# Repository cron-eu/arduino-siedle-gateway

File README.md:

Arduino Doorbell
====

Abstract
----

This repository holds the documentation and software needed to build a Slack interface to our Siedle Doorbell-System, using an Arduino MKR 1010 WiFi board and some electronics.

The gateway is being migrated to ESP32 / ESP-IDF (`firmware-idf/`), which will also add audio support. Until the new firmware runs in production, the Arduino firmware stays in `firmware/`.

Project Folder Structure
---

* `firmware-idf/**` New firmware for ESP32 / ESP32-S3 boards (ESP-IDF, C), see [firmware-idf/README.md](firmware-idf/README.md)
* `firmware/**` Firmware for the Arduino MKR1010 WiFi Board (C++)
* `lambda/**` AWS Lambda functions (Slack integration)
* `hardware/**` Schematics (Eagle)
* `doc/**` Documentation, see [doc/README.md](doc/README.md)

Author
----

Remus Lazar (rl -at- cron dot eu)

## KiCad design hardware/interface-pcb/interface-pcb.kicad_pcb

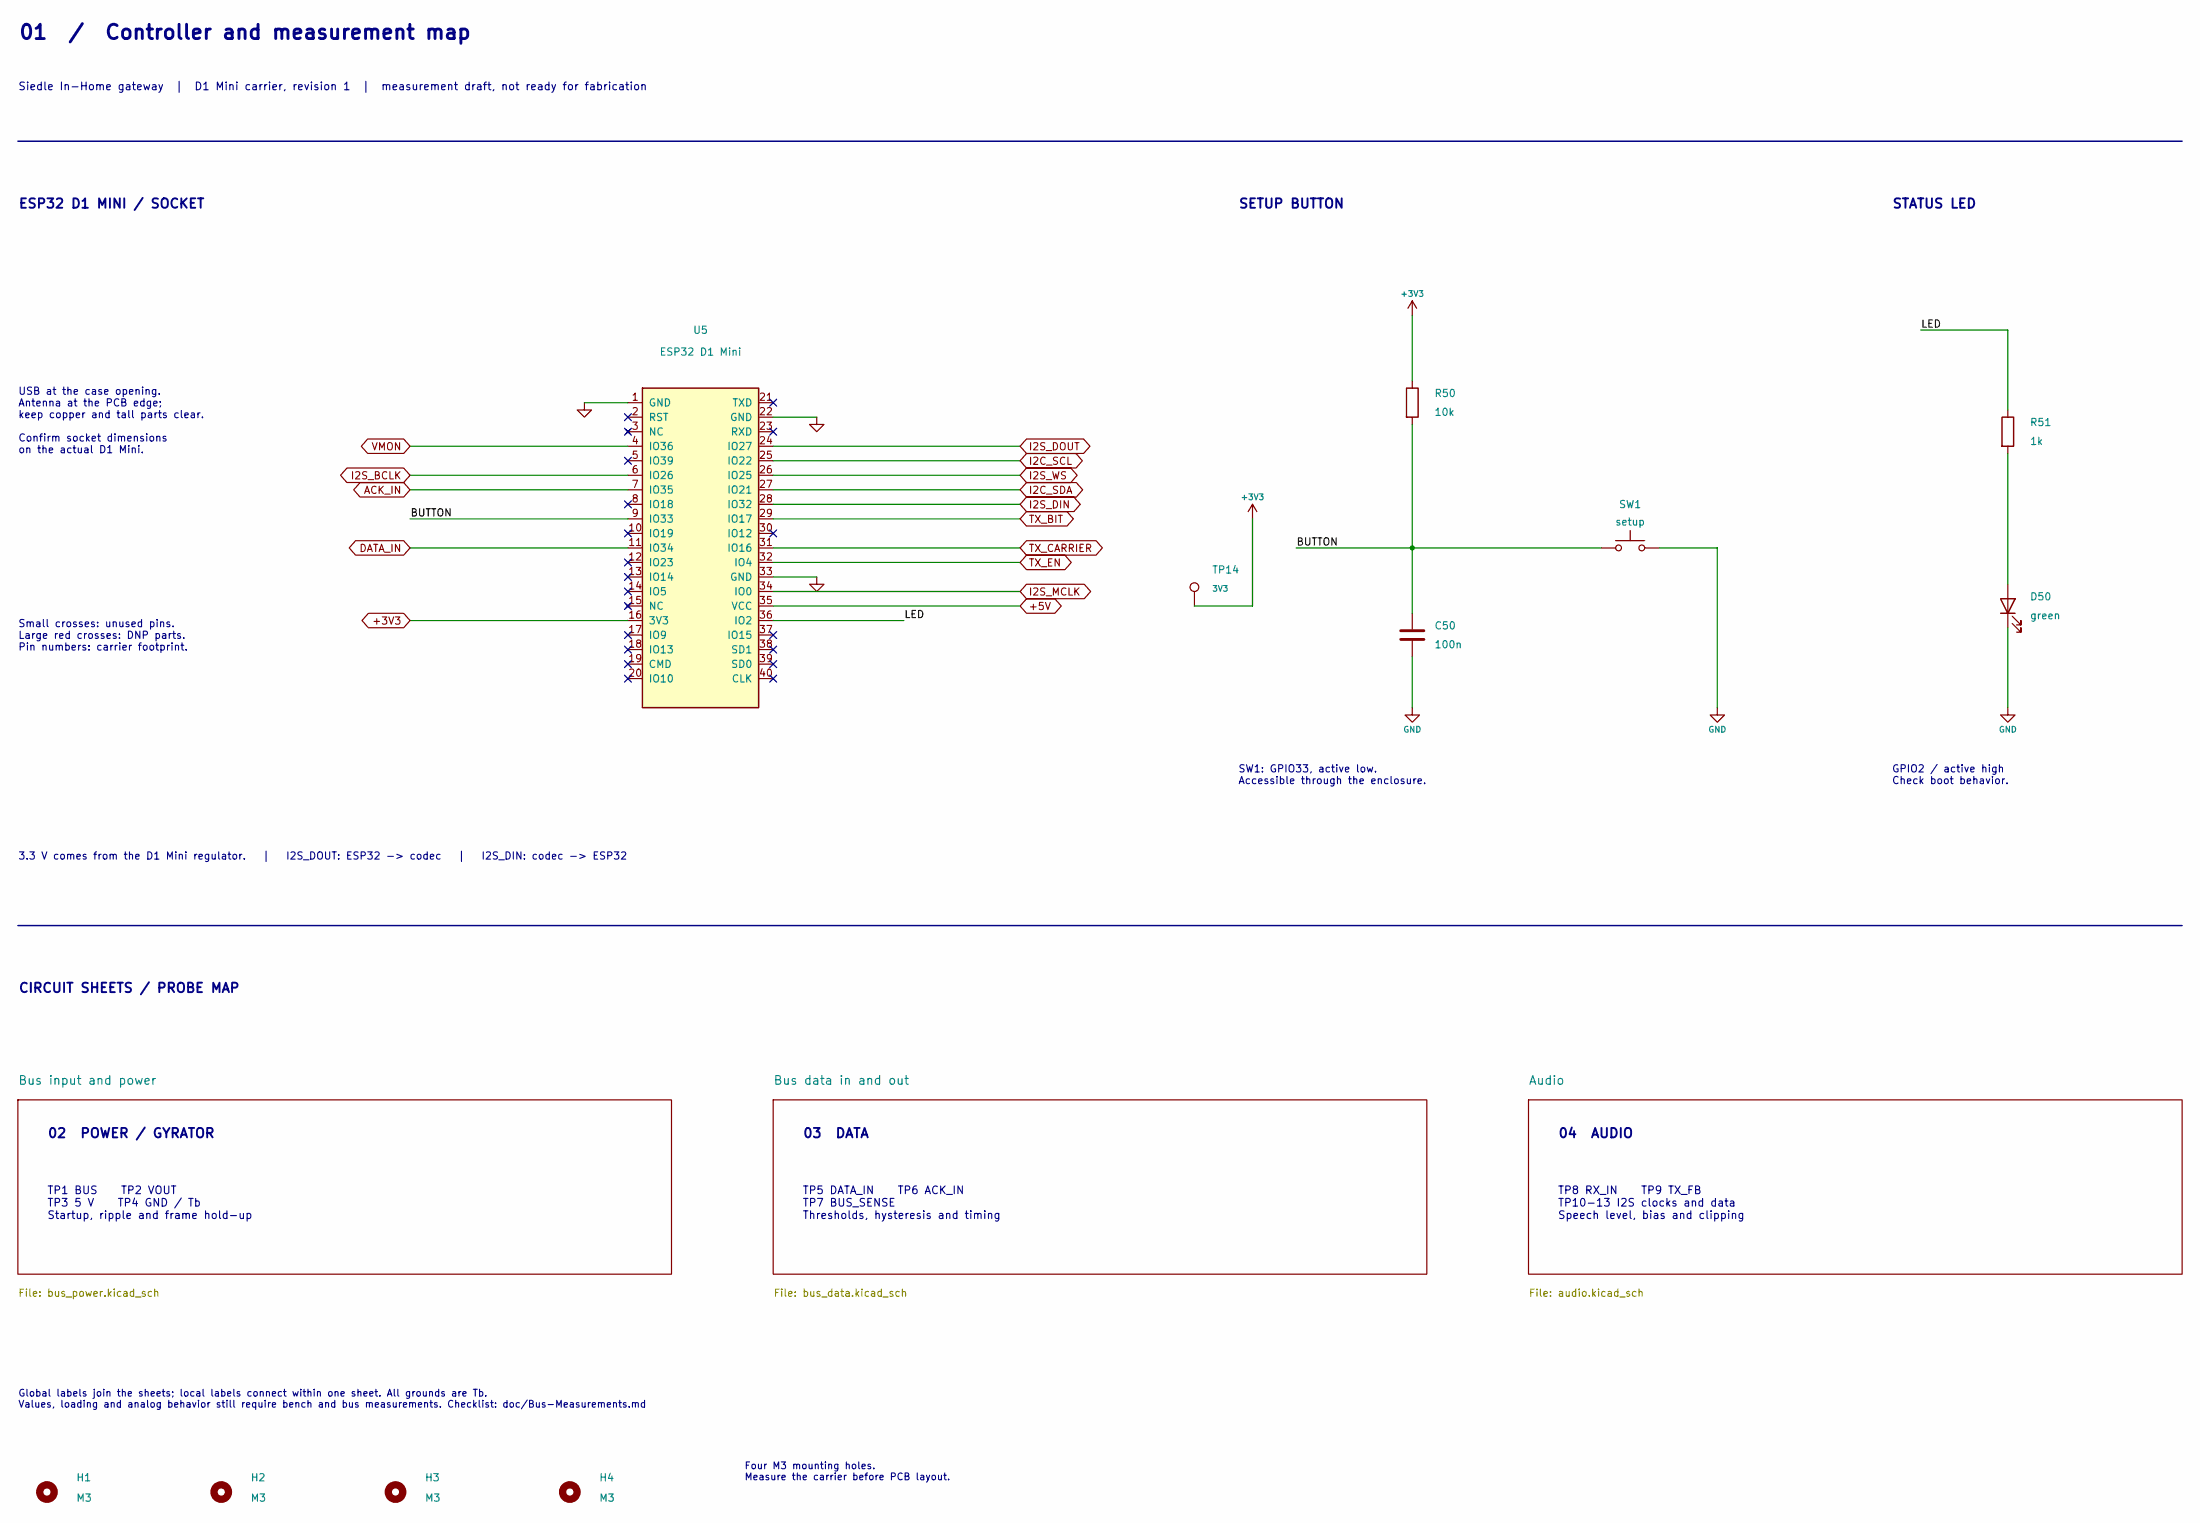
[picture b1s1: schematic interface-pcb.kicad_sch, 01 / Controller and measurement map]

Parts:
C50: 100n; C_0805_2012Metric; LCSC C49678
D50: green; LED_0805_2012Metric; LCSC C2297
H1, H2, H3, H4: M3; MountingHole_3.2mm_M3
R50: 10k; R_0805_2012Metric; LCSC C17414
R51: 1k; R_0805_2012Metric
SW1: setup; SW_Push_1P1T_XKB_TS-1187A; LCSC C318884
TP14: 3V3; TestPoint_Pad_D1.5mm
U5: ESP32 D1 Mini; D1_Mini_ESP32_Socket

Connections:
+3V3: R50.1, TP14.1, U5.16 (3V3); also elsewhere on the board
/BUTTON: C50.1, R50.2, SW1.1, U5.9 (IO33)
/LED: R51.1, U5.36 (IO2)
ACK_IN: U5.7 (IO35); also elsewhere on the board
DATA_IN: U5.11 (IO34); also elsewhere on the board
I2C_SCL: U5.25 (IO22); also elsewhere on the board
I2C_SDA: U5.27 (IO21); also elsewhere on the board
I2S_BCLK: U5.6 (IO26); also elsewhere on the board
I2S_DIN: U5.28 (IO32); also elsewhere on the board
I2S_DOUT: U5.24 (IO27); also elsewhere on the board
I2S_MCLK: U5.34 (IO0); also elsewhere on the board
I2S_WS: U5.26 (IO25); also elsewhere on the board
unnamed: D50.2 (A), R51.2
TX_BIT: U5.29 (IO17); also elsewhere on the board
TX_CARRIER: U5.31 (IO16); also elsewhere on the board
TX_EN: U5.32 (IO4); also elsewhere on the board
VMON: U5.4 (IO36); also elsewhere on the board

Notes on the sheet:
01 / Controller and measurement map
Siedle In-Home gateway | D1 Mini carrier, revision 1 | measurement draft, not ready for fabrication
ESP32 D1 MINI / SOCKET
SETUP BUTTON
STATUS LED
USB at the case opening. Antenna at the PCB edge; keep copper and tall parts clear. Confirm socket dimensions on the actual D1 Mini.
Small crosses: unused pins. Large red crosses: DNP parts. Pin numbers: carrier footprint.
SW1: GPIO33, active low. Accessible through the enclosure.
GPIO2 / active high Check boot behavior.
3.3 V comes from the D1 Mini regulator. | I2S_DOUT: ESP32 -> codec | I2S_DIN: codec -> ESP32
CIRCUIT SHEETS / PROBE MAP
02 POWER / GYRATOR
TP1 BUS TP2 VOUT TP3 5 V TP4 GND / Tb Startup, ripple and frame hold-up
03 DATA
TP5 DATA_IN TP6 ACK_IN TP7 BUS_SENSE Thresholds, hysteresis and timing
04 AUDIO
TP8 RX_IN TP9 TX_FB TP10-13 I2S clocks and data Speech level, bias and clipping
Global labels join the sheets; local labels connect within one sheet. All grounds are Tb. Values, loading and analog behavior still require bench and bus measurements. Checklist: doc/Bus-Measurements.md
Four M3 mounting holes. Measure the carrier before PCB layout.

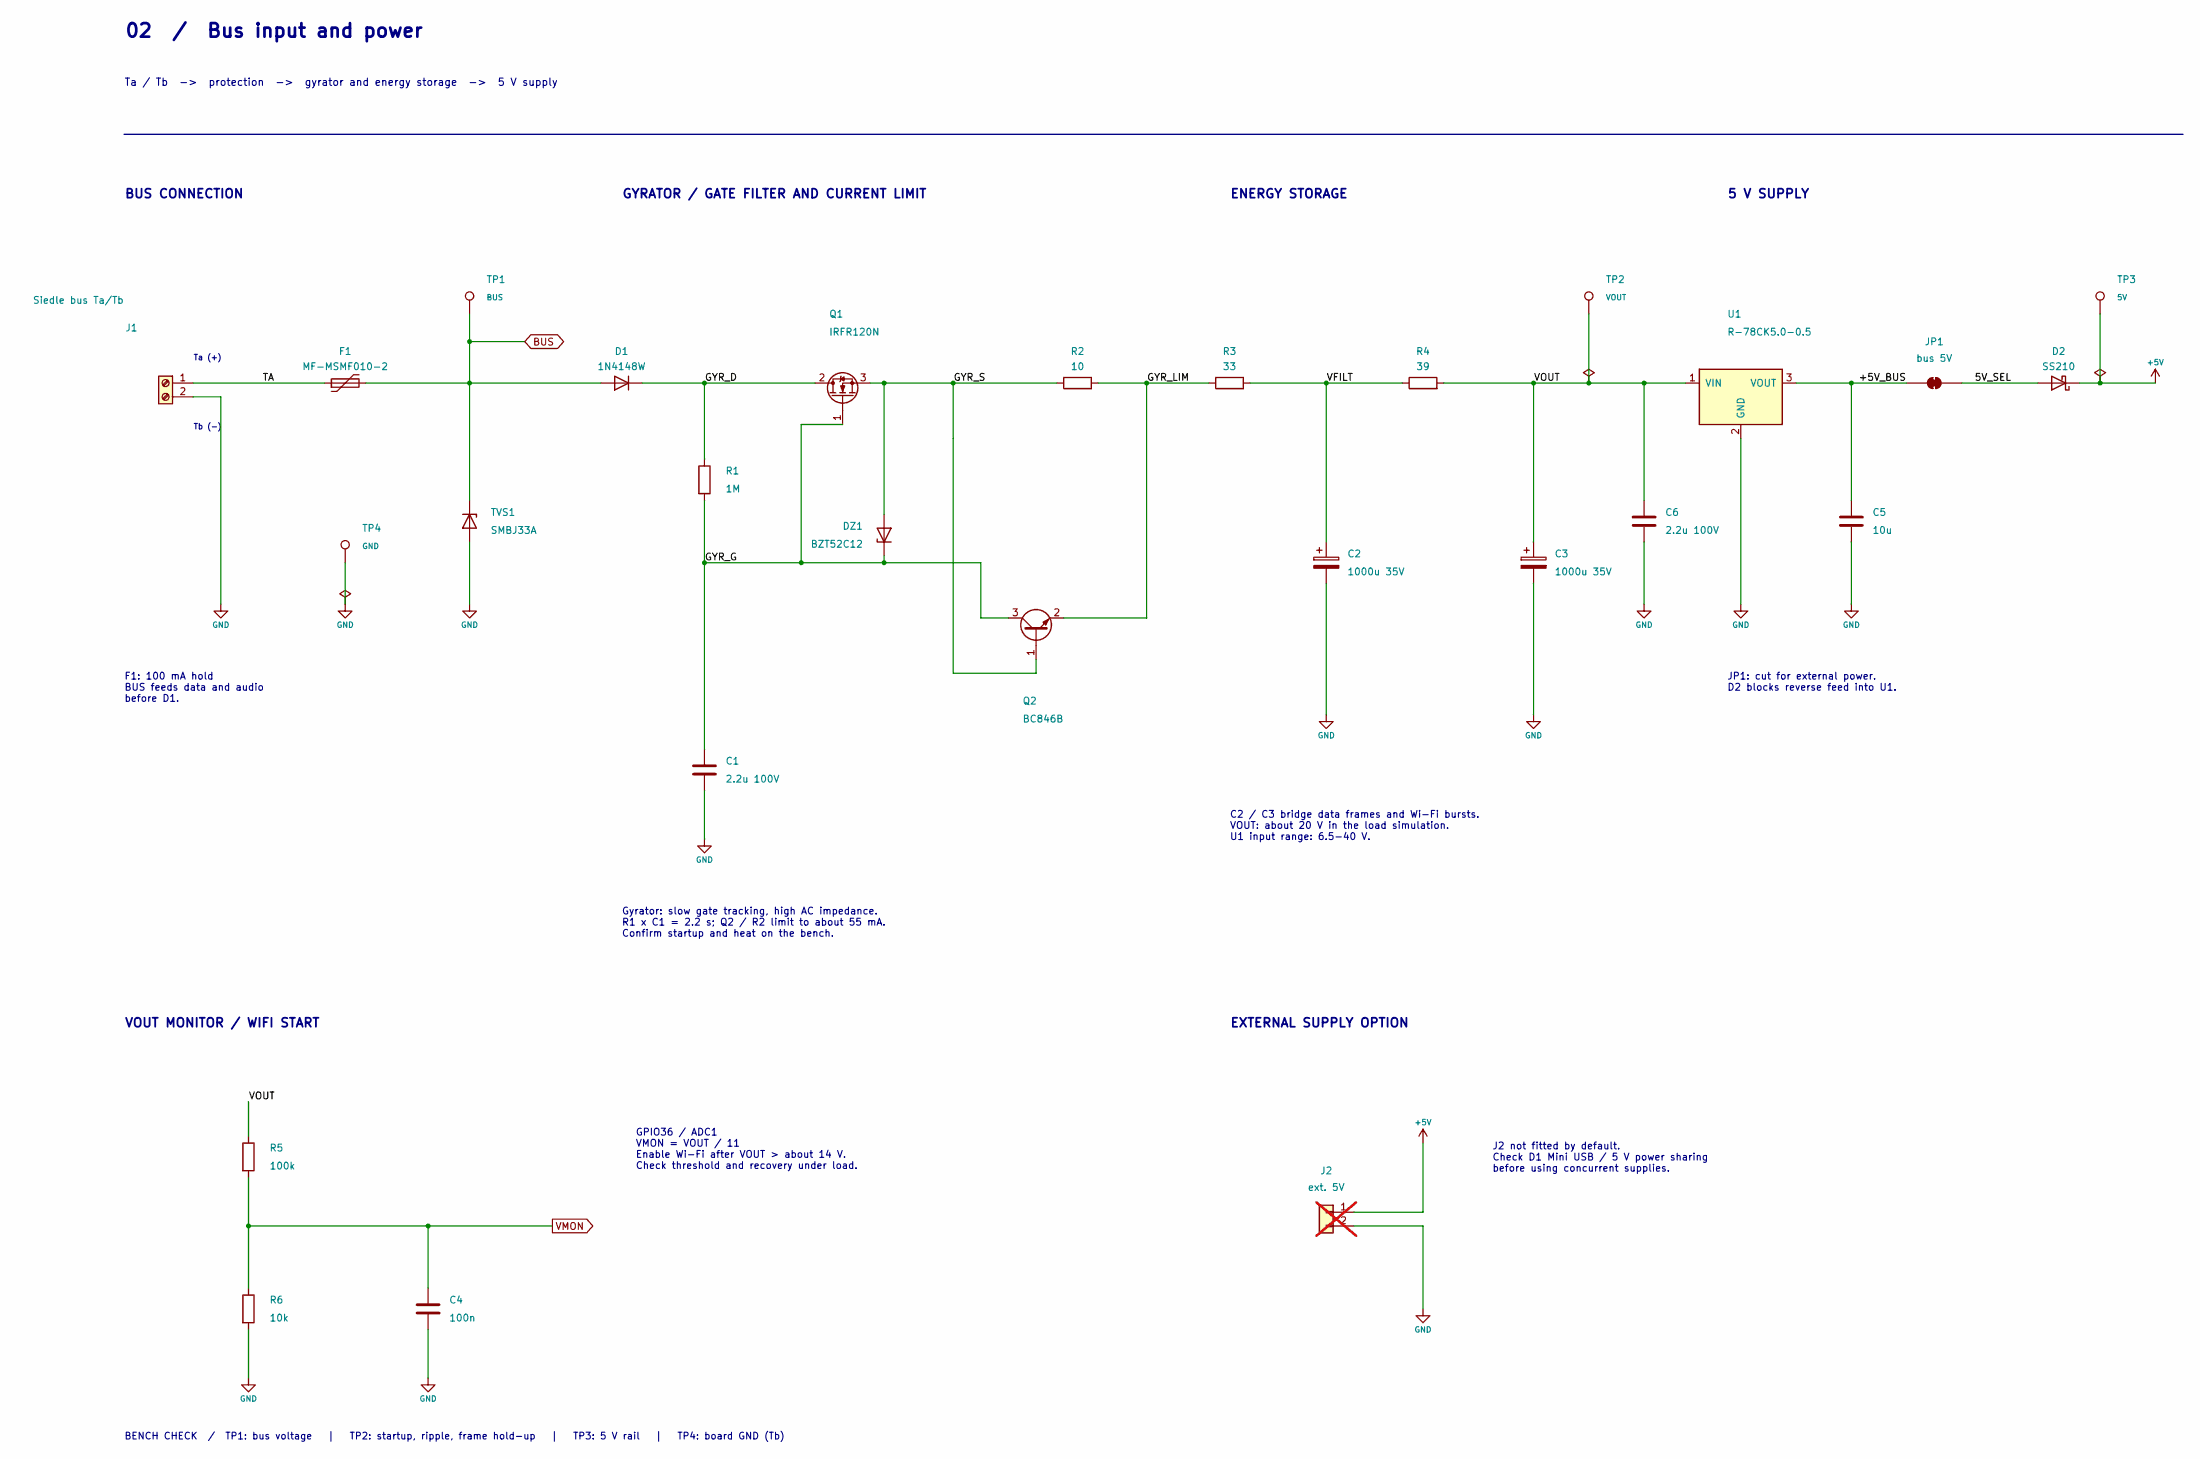
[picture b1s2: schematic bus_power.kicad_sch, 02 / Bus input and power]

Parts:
C1, C6: 2.2u 100V; C_1210_3225Metric; LCSC C153036
C2, C3: 1000u 35V; CP_Radial_D13.0mm_P5.00mm_Lying; LCSC C10749
C4: 100n; C_0805_2012Metric; LCSC C49678
C5: 10u; C_0805_2012Metric; LCSC C15850
D1: 1N4148W; D_SOD-123; LCSC C81598
D2: SS210; D_SMA; LCSC C14996
DZ1: BZT52C12; D_SOD-123; LCSC C19077410
F1: MF-MSMF010-2; Fuse_1812_4532Metric; LCSC C12430
J1: Siedle bus Ta/Tb; TerminalBlock_Phoenix_MKDS-1,5-2-5.08_1x02_P5.08mm_Horizont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; LCSC C474952
J2: ext. 5V; PinHeader_1x02_P2.54mm_Vertical; not fitted
JP1: bus 5V; SolderJumper-2_P1.3mm_Bridged_RoundedPad1.0x1.5mm
Q1: IRFR120N; TO-252-2; LCSC C3008
Q2: BC846B; SOT-23; LCSC C20069134
R1: 1M; R_0805_2012Metric; LCSC C17514
R2: 10; R_0805_2012Metric; LCSC C17415
R3: 33; R_0805_2012Metric; LCSC C17634
R4: 39; R_0805_2012Metric
R5: 100k; R_0805_2012Metric; LCSC C149504
R6: 10k; R_0805_2012Metric; LCSC C17414
TP1: BUS; TestPoint_Pad_D1.5mm
TP2: VOUT; TestPoint_Pad_D1.5mm
TP3: 5V; TestPoint_Pad_D1.5mm
TP4: GND; TestPoint_Pad_D1.5mm
TVS1: SMBJ33A; D_SMB; LCSC C19077586
U1: R-78CK5.0-0.5; Converter_DCDC_RECOM_R-78E-0.5_THT

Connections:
/Bus input and power/5V_SEL: D2.2 (A), JP1.2 (B)
/Bus input and power/+5V_BUS: C5.1, JP1.1 (A), U1.3 (VOUT)
/Bus input and power/GYR_D: D1.1 (K), Q1.2 (D), R1.1
/Bus input and power/GYR_G: C1.1, DZ1.1 (K), Q1.1 (G), Q2.3 (C), R1.2
/Bus input and power/GYR_LIM: Q2.2 (E), R2.2, R3.1
/Bus input and power/GYR_S: DZ1.2 (A), Q1.3 (S), Q2.1 (B), R2.1
/Bus input and power/TA: F1.1, J1.1
/Bus input and power/VFILT: C2.1, R3.2, R4.1
BUS: D1.2 (A), F1.2, TP1.1, TVS1.1 (K); also elsewhere on the board
VMON: C4.1, R5.2, R6.1; also elsewhere on the board

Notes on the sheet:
02 / Bus input and power
Ta / Tb -> protection -> gyrator and energy storage -> 5 V supply
BUS CONNECTION
GYRATOR / GATE FILTER AND CURRENT LIMIT
ENERGY STORAGE
5 V SUPPLY
Ta (+)
Tb (-)
F1: 100 mA hold BUS feeds data and audio before D1.
Gyrator: slow gate tracking, high AC impedance. R1 x C1 = 2.2 s; Q2 / R2 limit to about 55 mA. Confirm startup and heat on the bench.
C2 / C3 bridge data frames and Wi-Fi bursts. VOUT: about 20 V in the load simulation. U1 input range: 6.5-40 V.
JP1: cut for external power. D2 blocks reverse feed into U1.
VOUT MONITOR / WIFI START
GPIO36 / ADC1 VMON = VOUT / 11 Enable Wi-Fi after VOUT > about 14 V. Check threshold and recovery under load.
EXTERNAL SUPPLY OPTION
J2 not fitted by default. Check D1 Mini USB / 5 V power sharing before using concurrent supplies.
BENCH CHECK / TP1: bus voltage | TP2: startup, ripple, frame hold-up | TP3: 5 V rail | TP4: board GND (Tb)

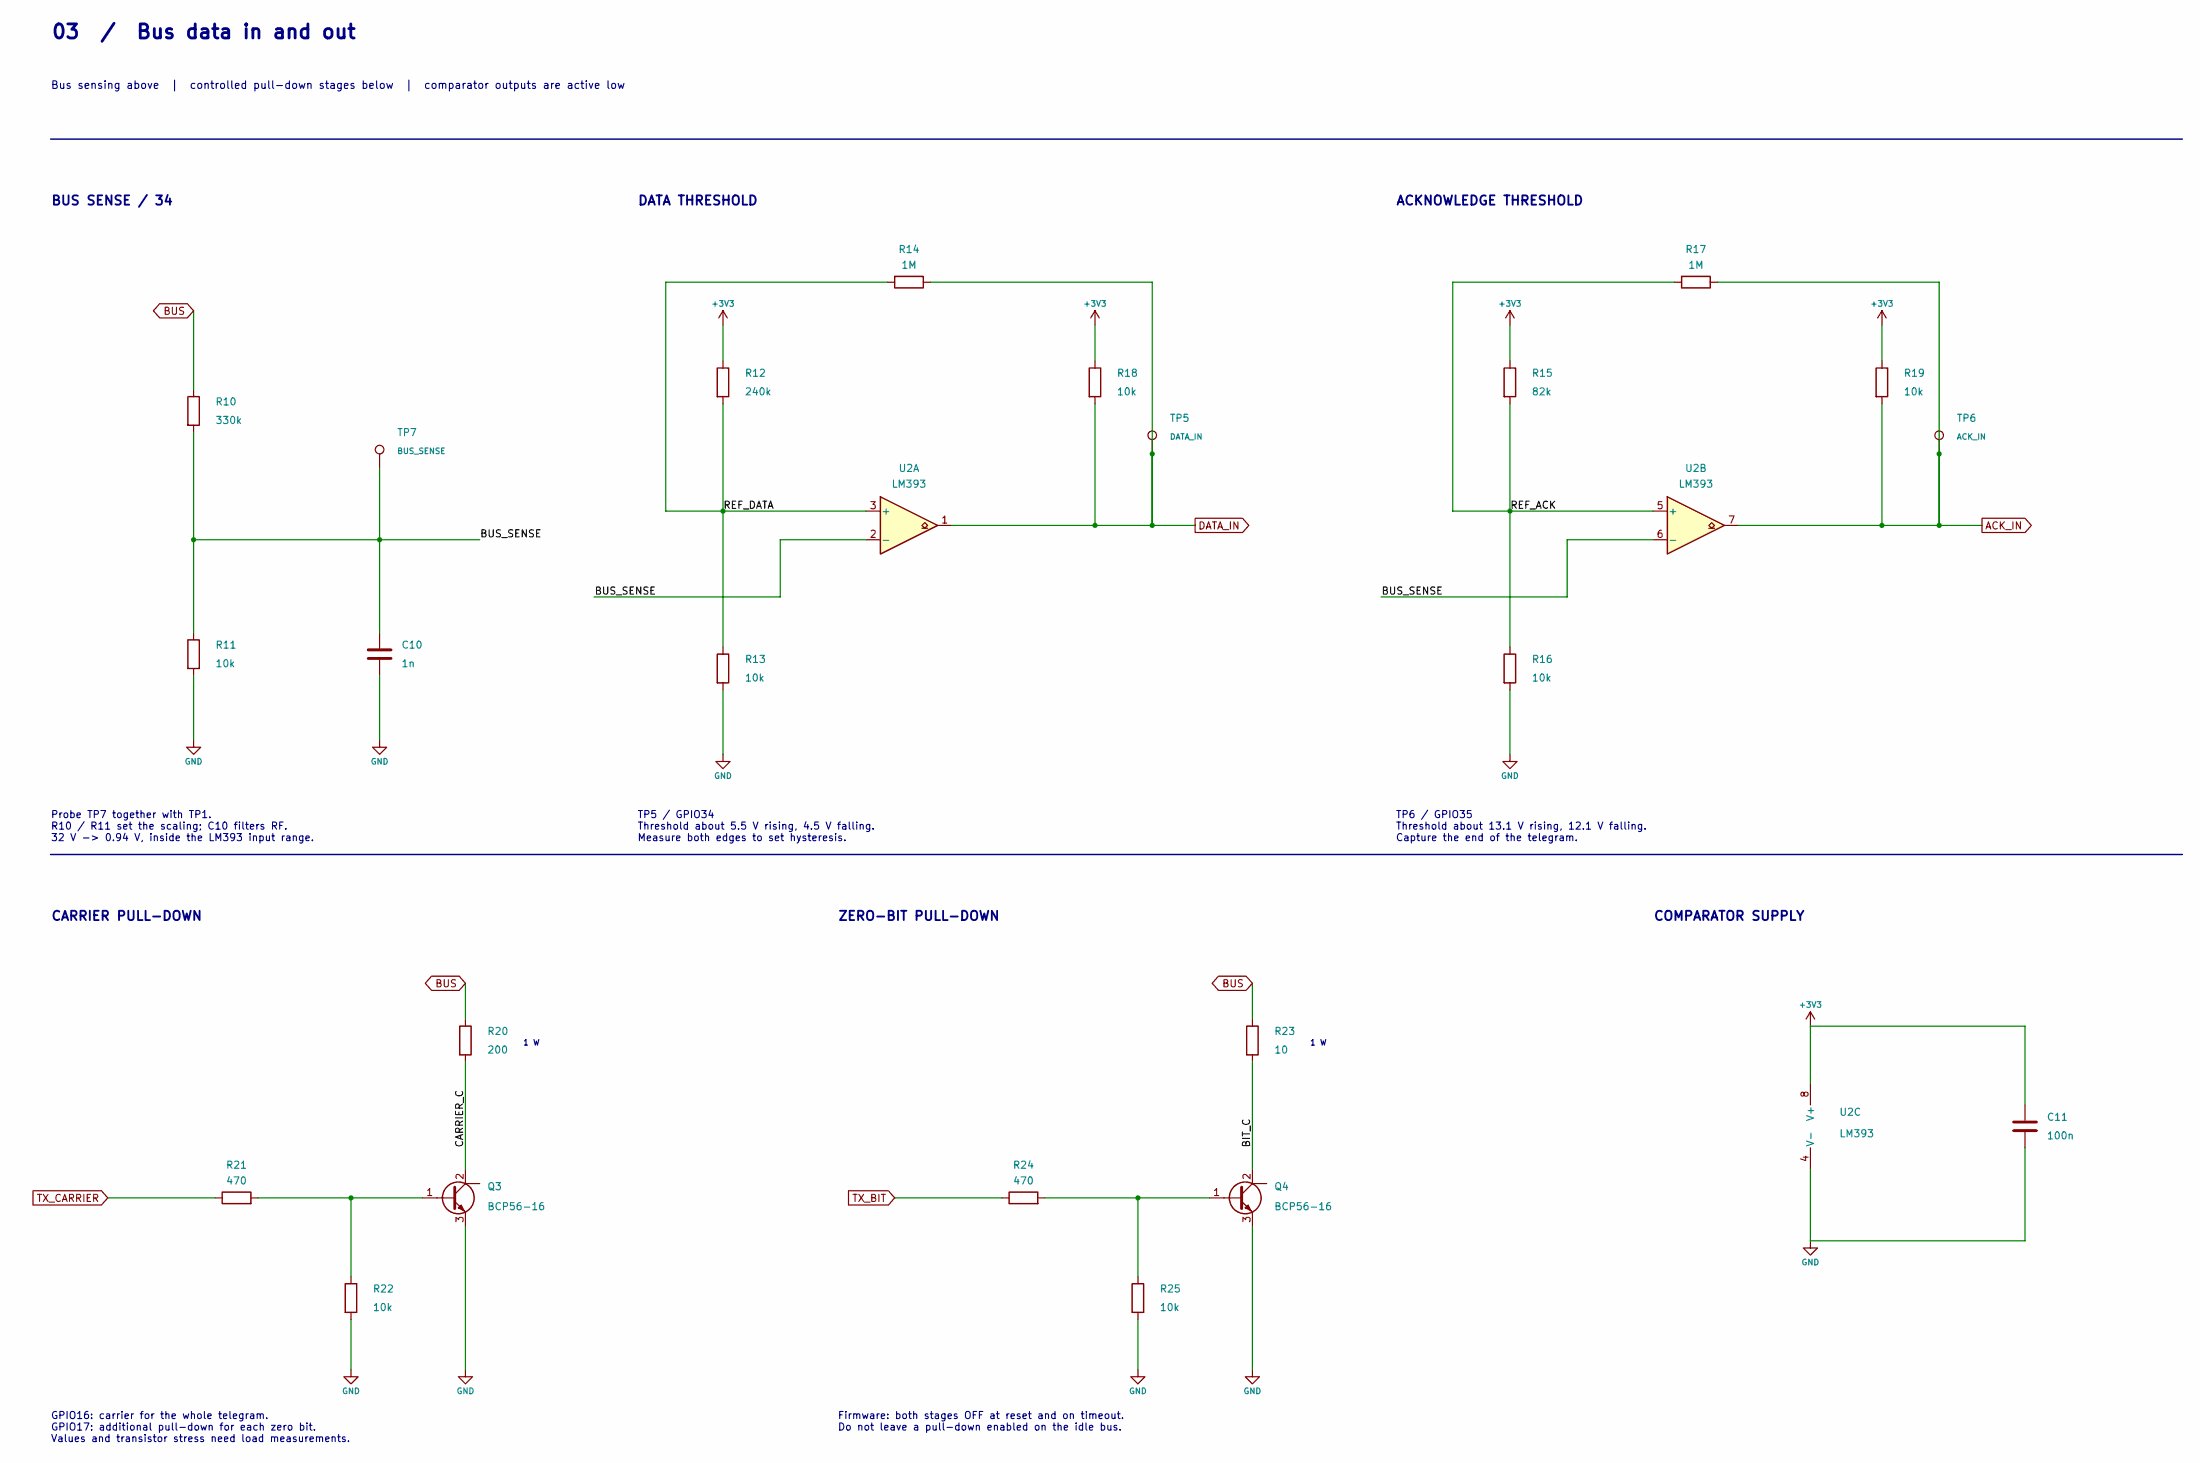
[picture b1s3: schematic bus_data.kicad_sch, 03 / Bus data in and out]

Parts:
C10: 1n; C_0805_2012Metric
C11: 100n; C_0805_2012Metric; LCSC C49678
Q3, Q4: BCP56-16; SOT-223-3_TabPin2; LCSC C41375109
R10: 330k; R_0805_2012Metric
R11, R13, R16, R18, R19, R22, R25: 10k; R_0805_2012Metric; LCSC C17414
R12: 240k; R_0805_2012Metric
R14, R17: 1M; R_0805_2012Metric; LCSC C17514
R15: 82k; R_0805_2012Metric
R20: 200; R_2512_6332Metric
R21, R24: 470; R_0805_2012Metric
R23: 10; R_2512_6332Metric
TP5: DATA_IN; TestPoint_Pad_D1.5mm
TP6: ACK_IN; TestPoint_Pad_D1.5mm
TP7: BUS_SENSE; TestPoint_Pad_D1.5mm
U2: LM393; SOIC-8_3.9x4.9mm_P1.27mm; LCSC C7955

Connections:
+3V3: C11.1, R12.1, R15.1, R18.1, R19.1, U2.8 (V+); also elsewhere on the board
/Bus data in and out/BIT_C: Q4.2 (C), R23.2
/Bus data in and out/BUS_SENSE: C10.1, R10.2, R11.1, TP7.1, U2.2 (-), U2.6 (-)
/Bus data in and out/CARRIER_C: Q3.2 (C), R20.2
/Bus data in and out/REF_ACK: R15.2, R16.1, R17.2, U2.5 (+)
/Bus data in and out/REF_DATA: R12.2, R13.1, R14.2, U2.3 (+)
ACK_IN: R17.1, R19.2, TP6.1, U2.7; also elsewhere on the board
BUS: R10.1, R20.1, R23.1; also elsewhere on the board
DATA_IN: R14.1, R18.2, TP5.1, U2.1; also elsewhere on the board
unnamed: Q3.1 (B), R21.2, R22.1
unnamed: Q4.1 (B), R24.2, R25.1
TX_BIT: R24.1; also elsewhere on the board
TX_CARRIER: R21.1; also elsewhere on the board

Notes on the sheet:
03 / Bus data in and out
Bus sensing above | controlled pull-down stages below | comparator outputs are active low
BUS SENSE / 34
DATA THRESHOLD
ACKNOWLEDGE THRESHOLD
Probe TP7 together with TP1. R10 / R11 set the scaling; C10 filters RF. 32 V -> 0.94 V, inside the LM393 input range.
TP5 / GPIO34 Threshold about 5.5 V rising, 4.5 V falling. Measure both edges to set hysteresis.
TP6 / GPIO35 Threshold about 13.1 V rising, 12.1 V falling. Capture the end of the telegram.
CARRIER PULL-DOWN
ZERO-BIT PULL-DOWN
COMPARATOR SUPPLY
1 W
GPIO16: carrier for the whole telegram. GPIO17: additional pull-down for each zero bit. Values and transistor stress need load measurements.
Firmware: both stages OFF at reset and on timeout. Do not leave a pull-down enabled on the idle bus.

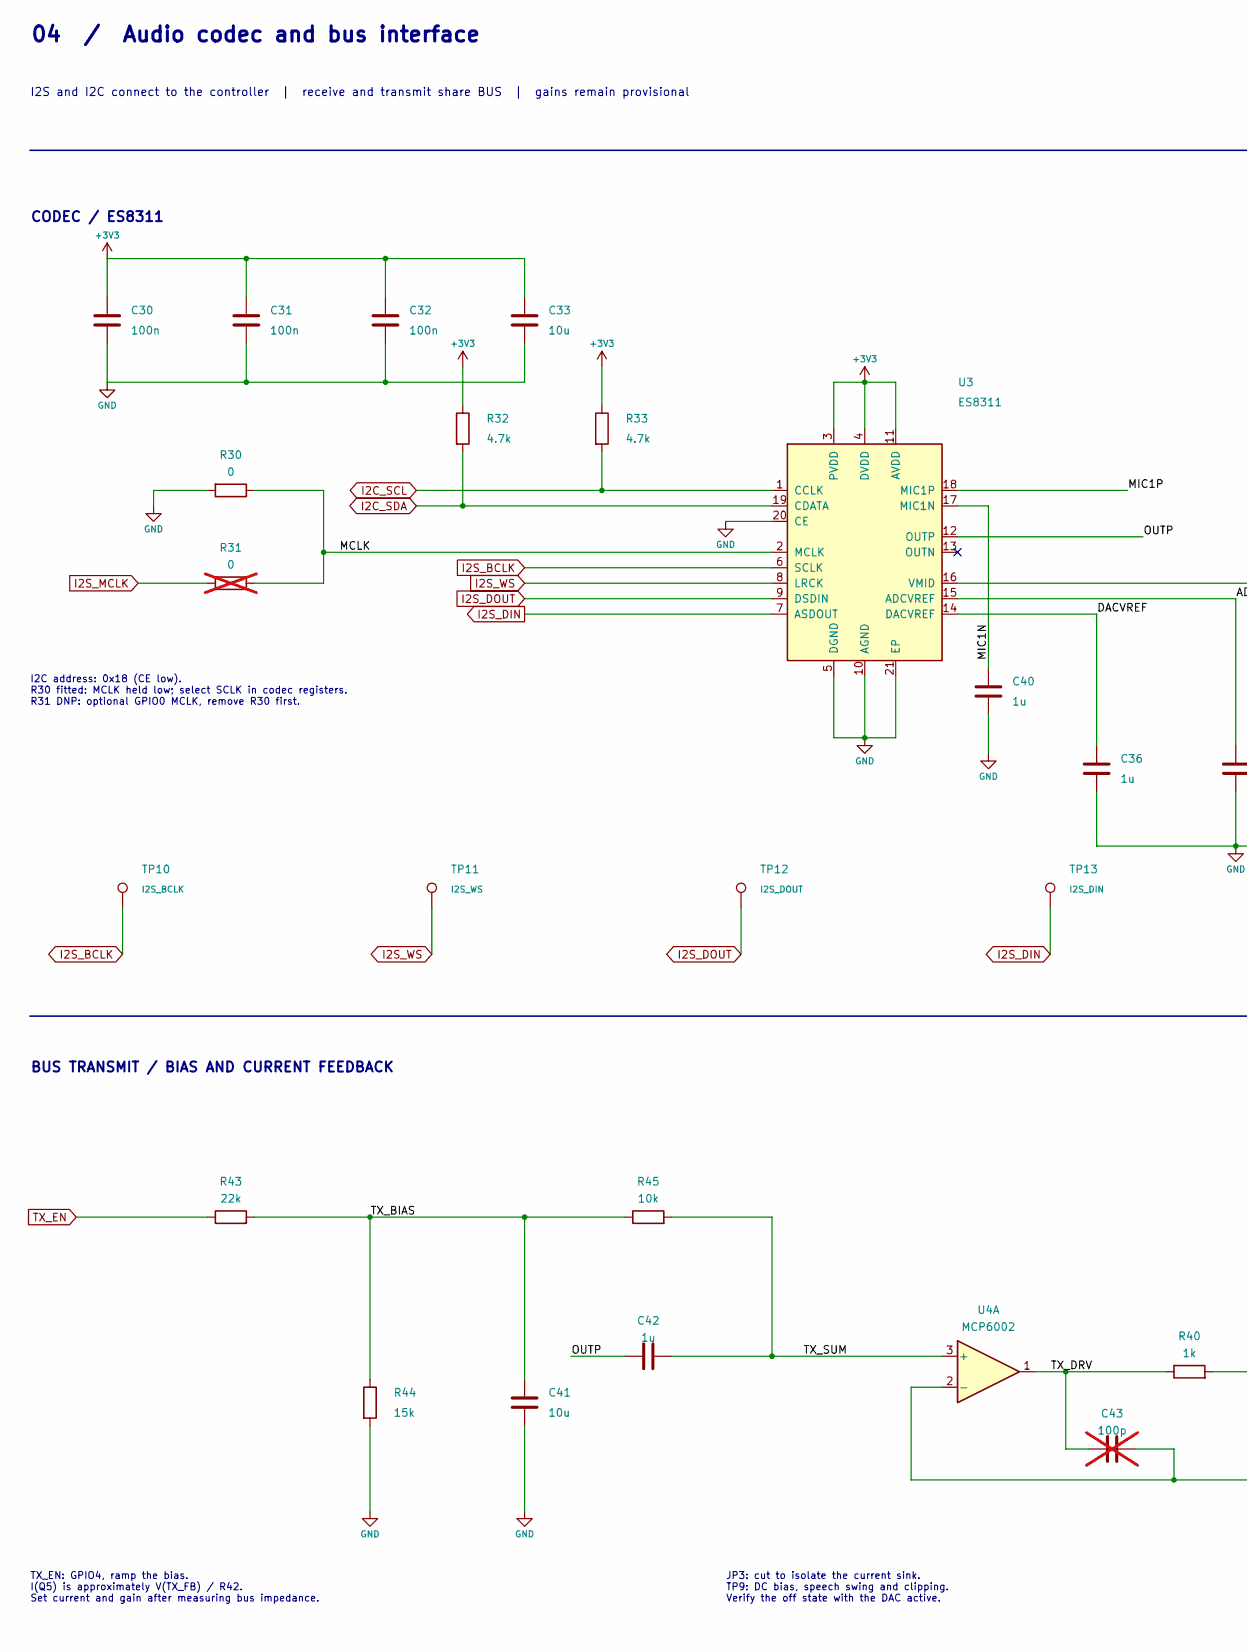
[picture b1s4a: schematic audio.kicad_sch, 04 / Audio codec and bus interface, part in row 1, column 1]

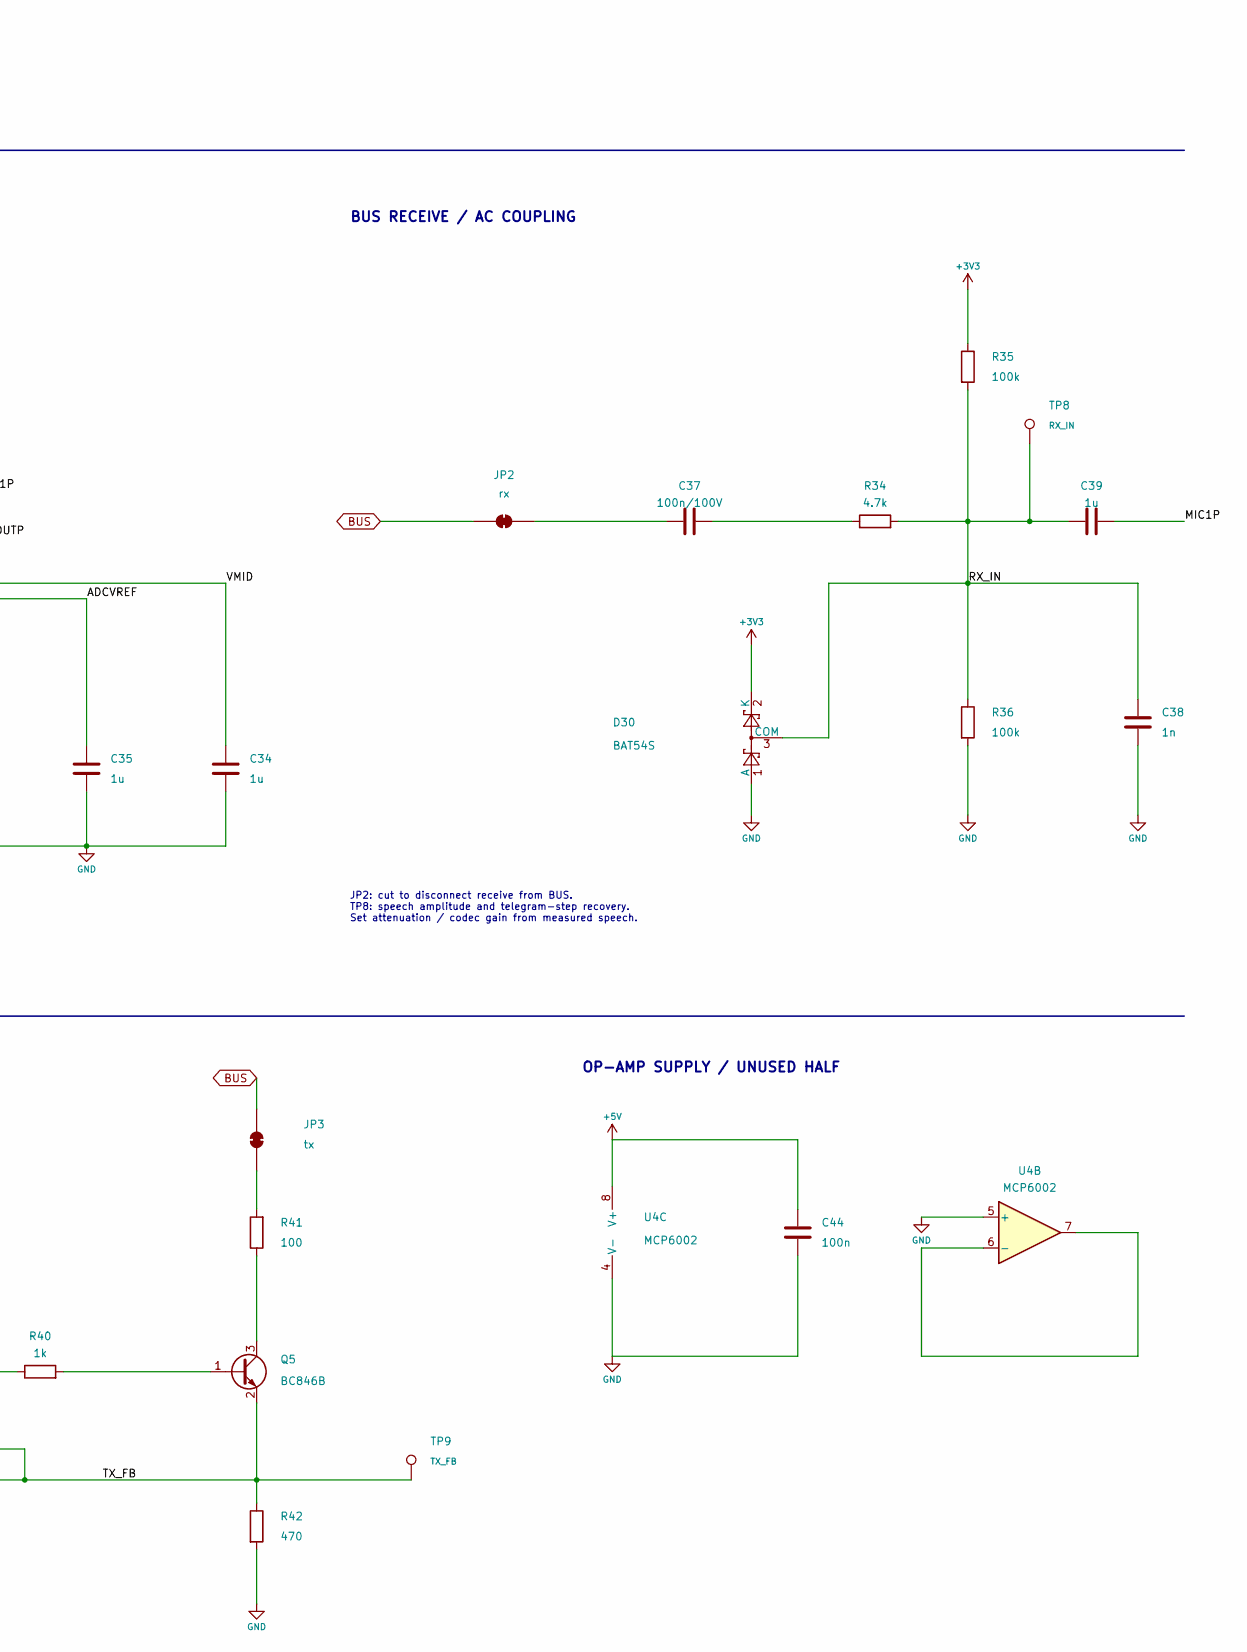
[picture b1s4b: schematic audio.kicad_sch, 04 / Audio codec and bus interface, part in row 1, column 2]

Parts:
C30, C31, C32, C44: 100n; C_0805_2012Metric; LCSC C49678
C33, C41: 10u; C_0805_2012Metric; LCSC C15850
C34, C35, C36, C39, C40, C42: 1u; C_0805_2012Metric
C37: 100n/100V; C_0805_2012Metric; LCSC C28233
C38: 1n; C_0805_2012Metric
C43: 100p; C_0805_2012Metric; not fitted
D30: BAT54S; SOT-23
JP2: rx; SolderJumper-2_P1.3mm_Bridged_RoundedPad1.0x1.5mm
JP3: tx; SolderJumper-2_P1.3mm_Bridged_RoundedPad1.0x1.5mm
Q5: BC846B; SOT-23; LCSC C20069134
R30: 0; R_0805_2012Metric
R31: 0; R_0805_2012Metric; not fitted
R32, R33, R34: 4.7k; R_0805_2012Metric; LCSC C17673
R35, R36: 100k; R_0805_2012Metric; LCSC C149504
R40: 1k; R_0805_2012Metric
R41: 100; R_0805_2012Metric
R42: 470; R_0805_2012Metric
R43: 22k; R_0805_2012Metric
R44: 15k; R_0805_2012Metric
R45: 10k; R_0805_2012Metric; LCSC C17414
TP8: RX_IN; TestPoint_Pad_D1.5mm
TP9: TX_FB; TestPoint_Pad_D1.5mm
TP10: I2S_BCLK; TestPoint_Pad_D1.5mm
TP11: I2S_WS; TestPoint_Pad_D1.5mm
TP12: I2S_DOUT; TestPoint_Pad_D1.5mm
TP13: I2S_DIN; TestPoint_Pad_D1.5mm
U3: ES8311; QFN-20-1EP_3x3mm_P0.4mm_EP1.65x1.65mm; LCSC C962342
U4: MCP6002; SOIC-8_3.9x4.9mm_P1.27mm; LCSC C7377

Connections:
+3V3: C30.1, C31.1, C32.1, C33.1, D30.2 (K), R32.1, R33.1, R35.1, U3.3 (PVDD), U3.4 (DVDD), U3.11 (AVDD); also elsewhere on the board
/Audio/ADCVREF: C35.1, U3.15 (ADCVREF)
/Audio/DACVREF: C36.1, U3.14 (DACVREF)
/Audio/MCLK: R30.1, R31.1, U3.2 (MCLK)
/Audio/MIC1N: C40.1, U3.17 (MIC1N)
/Audio/MIC1P: C39.2, U3.18 (MIC1P)
/Audio/OUTP: C42.1, U3.12 (OUTP)
/Audio/RX_IN: C38.1, C39.1, D30.3 (COM), R34.2, R35.2, R36.1, TP8.1
/Audio/TX_BIAS: C41.1, R43.2, R44.1, R45.1
/Audio/TX_DRV: C43.1, R40.1, U4.1
/Audio/TX_FB: C43.2, Q5.2 (E), R42.1, TP9.1, U4.2 (-)
/Audio/TX_SUM: C42.2, R45.2, U4.3 (+)
/Audio/VMID: C34.1, U3.16 (VMID)
BUS: JP2.1 (A), JP3.2 (B); also elsewhere on the board
I2C_SCL: R33.2, U3.1 (CCLK); also elsewhere on the board
I2C_SDA: R32.2, U3.19 (CDATA); also elsewhere on the board
I2S_BCLK: TP10.1, U3.6 (SCLK); also elsewhere on the board
I2S_DIN: TP13.1, U3.7 (ASDOUT); also elsewhere on the board
I2S_DOUT: TP12.1, U3.9 (DSDIN); also elsewhere on the board
I2S_MCLK: R31.2; also elsewhere on the board
I2S_WS: TP11.1, U3.8 (LRCK); also elsewhere on the board
unnamed: C37.2, R34.1
unnamed: C37.1, JP2.2 (B)
unnamed: JP3.1 (A), R41.2
unnamed: Q5.1 (B), R40.2
unnamed: Q5.3 (C), R41.1
unnamed: U4.6 (-), U4.7
TX_EN: R43.1; also elsewhere on the board

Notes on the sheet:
04 / Audio codec and bus interface
I2S and I2C connect to the controller | receive and transmit share BUS | gains remain provisional
CODEC / ES8311
BUS RECEIVE / AC COUPLING
I2C address: 0x18 (CE low). R30 fitted: MCLK held low; select SCLK in codec registers. R31 DNP: optional GPIO0 MCLK, remove R30 first.
JP2: cut to disconnect receive from BUS. TP8: speech amplitude and telegram-step recovery. Set attenuation / codec gain from measured speech.
BUS TRANSMIT / BIAS AND CURRENT FEEDBACK
OP-AMP SUPPLY / UNUSED HALF
TX_EN: GPIO4, ramp the bias. I(Q5) is approximately V(TX_FB) / R42. Set current and gain after measuring bus impedance.
JP3: cut to isolate the current sink. TP9: DC bias, speech swing and clipping. Verify the off state with the DAC active.

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
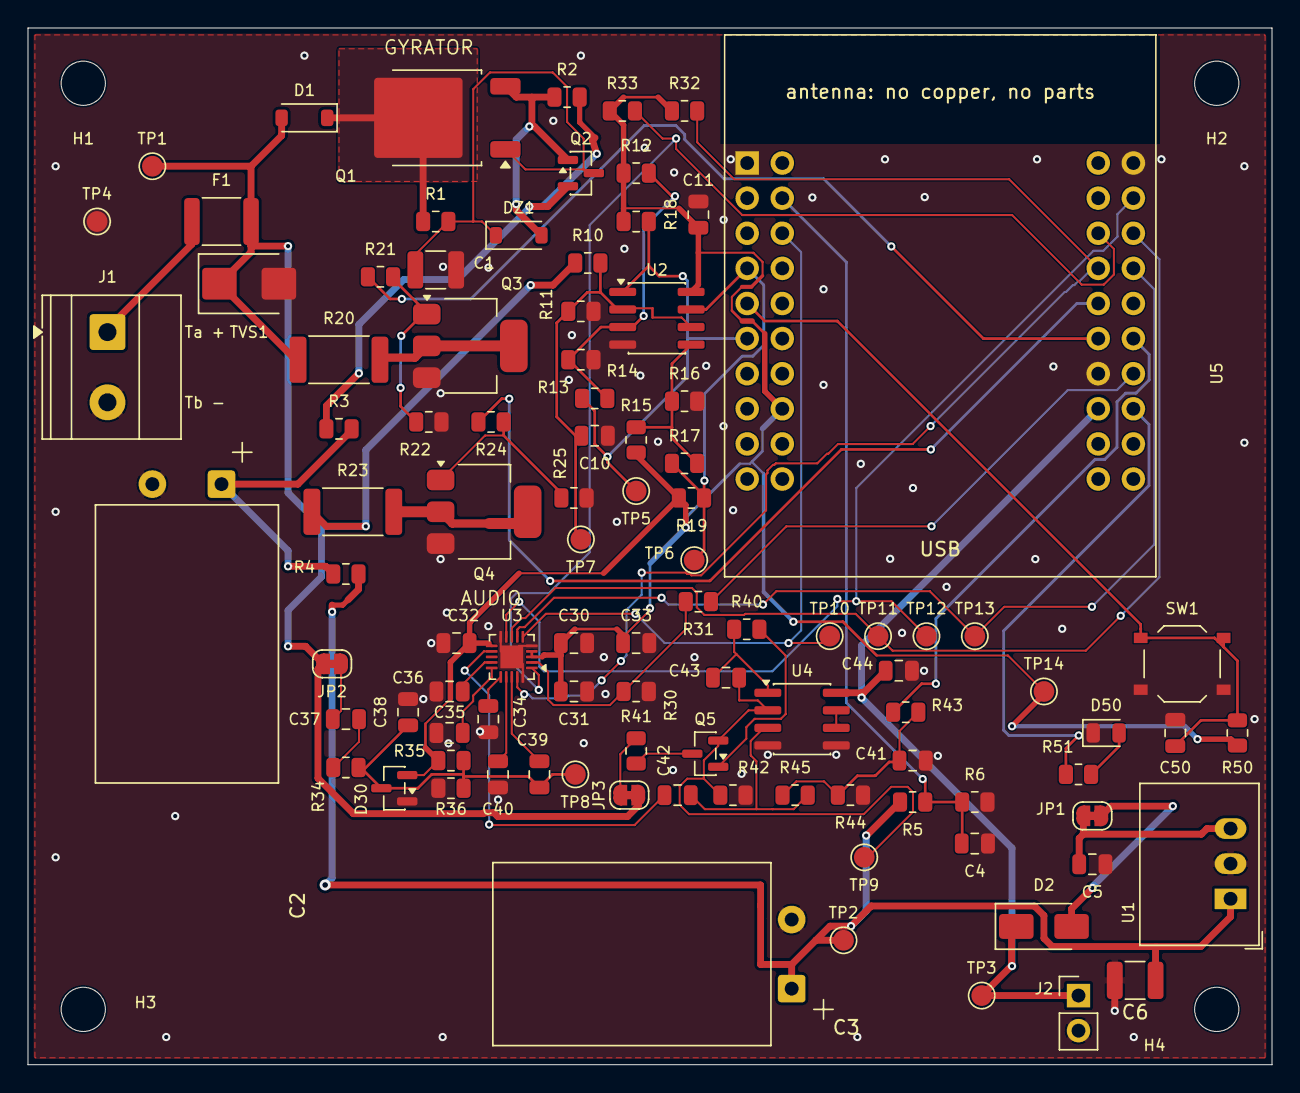
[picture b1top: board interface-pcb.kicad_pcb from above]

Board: 2 copper layers, 90.0 x 75.0 mm, 103 parts (0 on the bottom side), 54 nets.

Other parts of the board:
MK1: ESP32 D1 Mini, 3D only; D1_Mini_ESP32_Module_3D
